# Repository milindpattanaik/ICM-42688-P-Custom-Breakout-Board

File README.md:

# ICM-42688-P Breakout Board

## Overview

### What is the ICM-42688-P?
The **ICM-42688-P** is a high-performance **6-axis Inertial Measurement Unit (IMU)** that integrates a **3-axis gyroscope** and a **3-axis accelerometer** in a compact package. It offers **low noise, high stability, and precision motion tracking**, making it ideal for applications like **drones, robotics, and industrial motion sensing**.  

The sensor supports both **I2C and SPI** communication, features **programmable digital filters, FIFO buffering, and low power consumption**, and includes **two interrupt pins** for efficient data handling. Its **temperature stability and low drift** make it well-suited for demanding applications requiring **accurate inertial measurements**.

### About This Project
This project is a **custom breakout board** for the ICM-42688-P, designed using **KiCad 8.0**. It includes:
- **Hardware**: A compact PCB with **I2C & SPI support**, onboard **3.3V LDO**, and **interrupt pins**.
- **Firmware**: Example code using **PlatformIO (Arduino framework)** for easy testing.
- **Testing Guide**: Steps to set up and read sensor data over I2C & SPI.

The driver used for interfacing with the **ICM-42688-P** is an open-source implementation developed by [Inhwan Wee ](https://github.com/finani) and is hosted on [https://github.com/finani/ICM42688](https://github.com/finani/ICM42688). This driver provides a well-structured and efficient way to communicate with the sensor over I2C or SPI, enabling seamless integration with Arduino and PlatformIO environments.

## Hardware Design
### Features:
- **Power Supply**: 3.3V LDO regulator onboard
- **Communication**: Supports both **I2C (SDA/SCL)** and **SPI (SCK, SDI, SDO, CS)**
- **Interrupts**: `INT1` and `INT2` available
- **Jumpers**: Select between I2C and SPI modes
- **Designed in**: KiCad 8.0
- **Tested on**: PlatformIO with Arduino framework

### Schematic

### PCB Layout

## Software

### Fixing `<cstdint>` Issues with AVR-GCC  

When compiling for AVR-based boards (e.g., **Arduino Uno, Mega, etc.**) using **AVR-GCC**, you may encounter the following error:  

```sh
fatal error: cstdint: No such file or directory
```

This happens because **AVR-GCC does not fully support C++ standard headers like `<cstdint>`**. This is a common defect in the arduino library.  

### Solution: Use `<stdint.h>` Instead  
The best solution is to replace `<cstdint>` with `<stdint.h>` in the `registers.h` file of the driver src code.  

❌ **Incorrect:**  
```cpp
#include <cstdint>  // This may cause issues with AVR-GCC
```
✅ **Correct:**  
```cpp
#ifdef AVR  // If compiling for AVR, define NO_CSTDINT to prevent including <cstdint>
# define NO_CSTDINT 1
#endif

// If NO_CSTDINT is NOT defined, include the standard C++ <cstdint>
#ifndef NO_CSTDINT
# include <cstdint>
#else
# include <stdint.h>

// If <cstdint> is unavailable, manually provide the needed types.
namespace std {
  using ::int8_t;           
  using ::uint8_t;         
                     
  using ::int16_t;         
  using ::uint16_t;       
                     
  using ::int32_t;         
  using ::uint32_t;       
}

#endif
```
✅ `<stdint.h>` is the **C version of `<cstdint>`** and is fully compatible with AVR-GCC.

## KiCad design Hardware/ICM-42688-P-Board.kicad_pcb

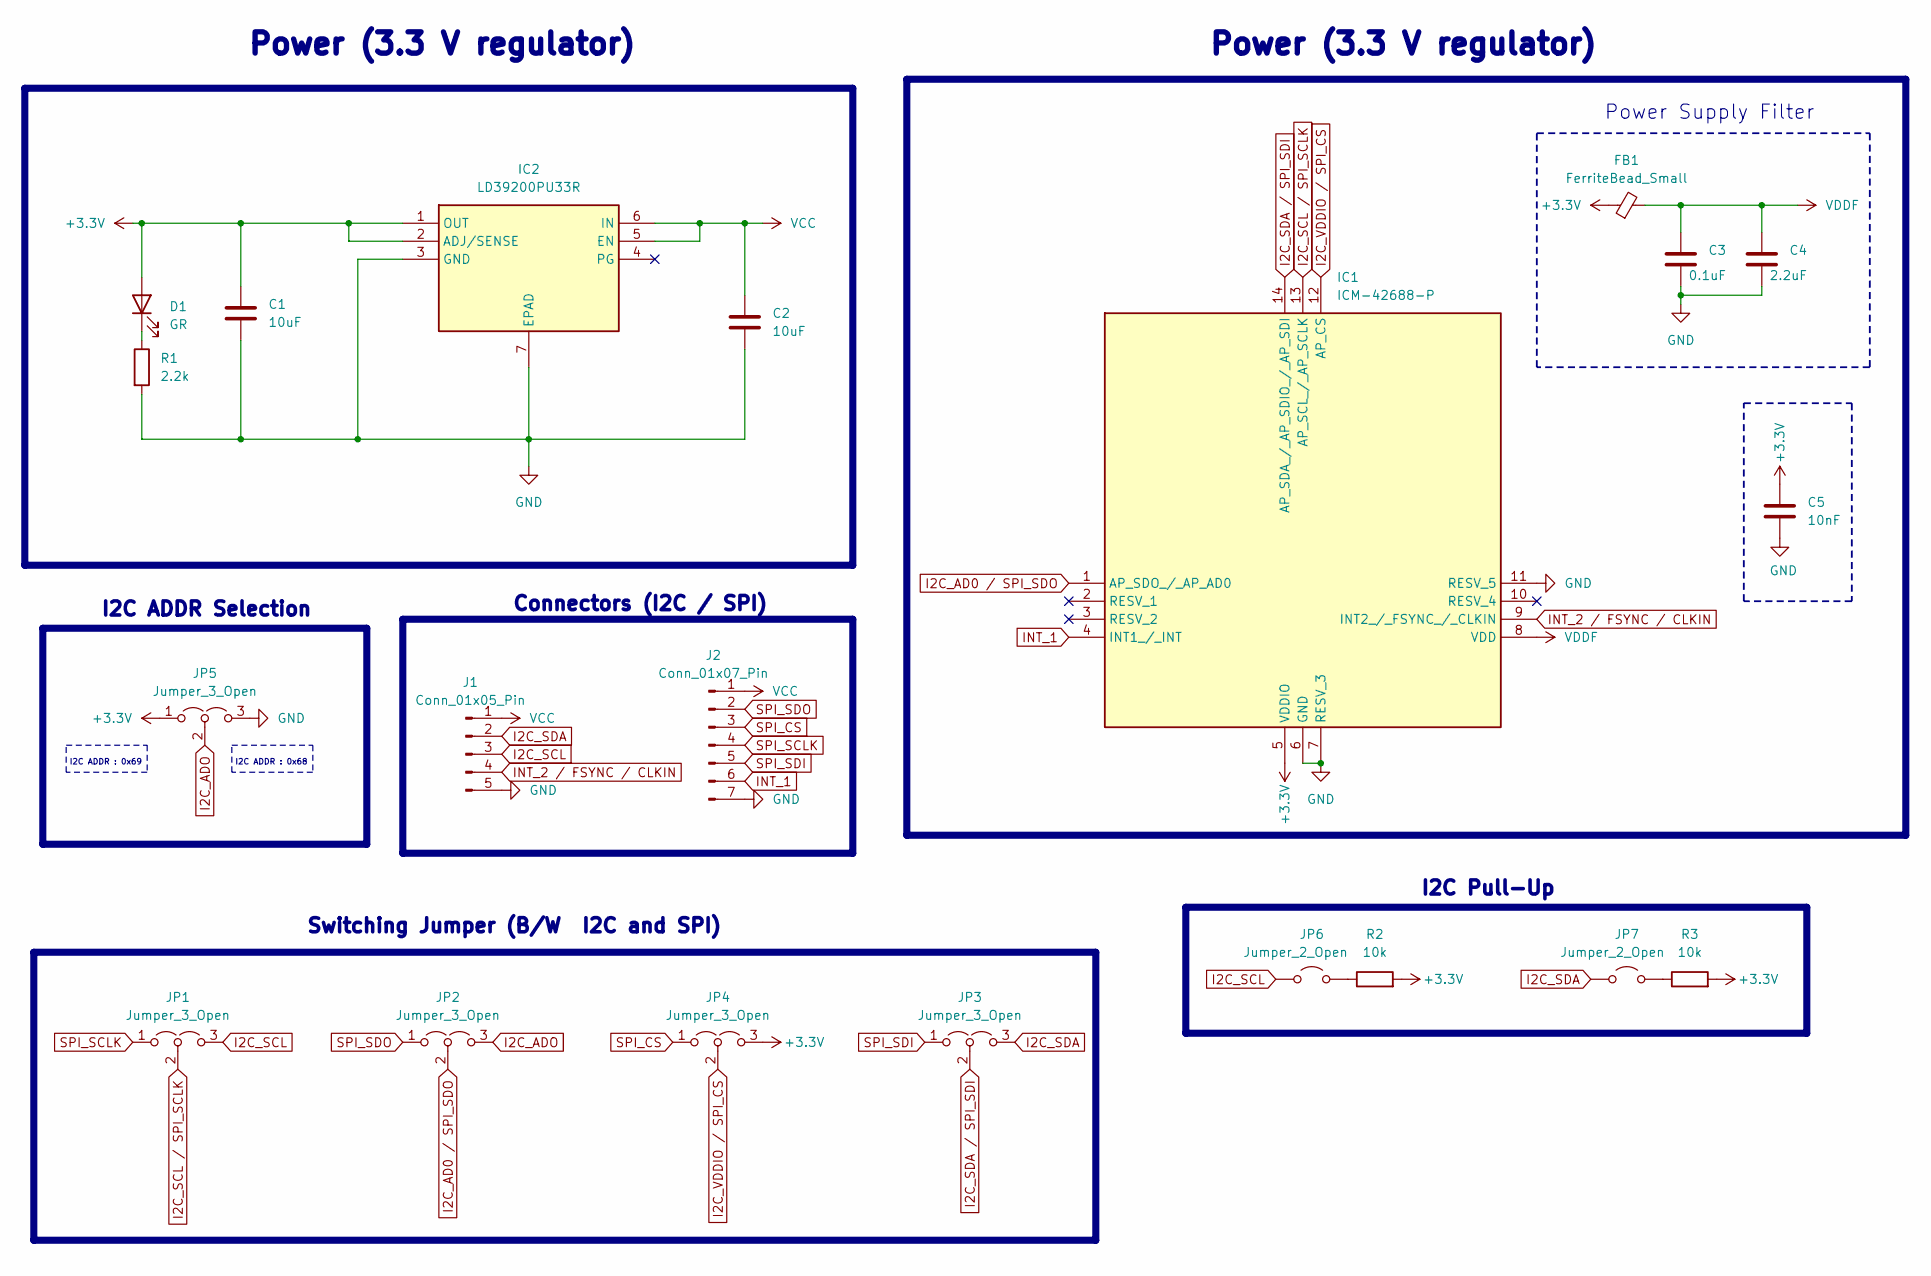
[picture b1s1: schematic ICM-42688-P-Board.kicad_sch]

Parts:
C1, C2: 10uF; C_0603_1608Metric
C3: 0.1uF; C_0402_1005Metric
C4: 2.2uF; C_0402_1005Metric
C5: 10nF; C_0402_1005Metric
D1: GR; LED_0603_1608Metric
FB1: FerriteBead_Small; L_0603_1608Metric
IC1: ICM-42688-P; IIM42352; Mouser Part Number 410-ICM-42688-P
IC2: LD39200PU33R; SON95P300X300X100-7N-D; Mouser Part Number 511-LD39200PU33R
J1: Conn_01x05_Pin; PinHeader_1x05_P2.54mm_Vertical
J2: Conn_01x07_Pin; PinHeader_1x07_P2.54mm_Vertical
JP1, JP2, JP3, JP4, JP5: Jumper_3_Open; PinHeader_1x03_P2.54mm_Vertical
JP6, JP7: Jumper_2_Open; PinHeader_1x02_P2.54mm_Vertical
R1: 2.2k; R_0402_1005Metric
R2, R3: 10k; R_0603_1608Metric

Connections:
+3.3V: C1.1, C5.1, D1.2 (A), FB1.1, IC1.5 (VDDIO), IC2.1 (OUT), IC2.2 (ADJ/SENSE), JP4.3 (B), JP5.1 (A), R2.2, R3.2
GND: C1.2, C2.2, C3.2, C4.2, C5.2, IC1.6 (GND), IC1.7 (RESV_3), IC1.11 (RESV_5), IC2.3 (GND), IC2.7 (EPAD), J1.5, J2.7, JP5.3 (B), R1.2; also elsewhere on the board
I2C_AD0 / SPI_SDO: IC1.1 (AP_SDO_/_AP_AD0), JP2.2 (C)
I2C_ADO: JP2.3 (B), JP5.2 (C)
I2C_SCL: J1.3, JP1.3 (B), JP6.1 (A)
I2C_SCL / SPI_SCLK: IC1.13 (AP_SCL_/_AP_SCLK), JP1.2 (C)
I2C_SDA: J1.2, JP3.3 (B), JP7.1 (A)
I2C_SDA / SPI_SDI: IC1.14 (AP_SDA_/_AP_SDIO_/_AP_SDI), JP3.2 (C)
I2C_VDDIO / SPI_CS: IC1.12 (AP_CS), JP4.2 (C)
INT_1: IC1.4 (INT1_/_INT), J2.6
INT_2 / FSYNC / CLKIN: IC1.9 (INT2_/_FSYNC_/_CLKIN), J1.4
unnamed: D1.1 (K), R1.1
unnamed: JP6.2 (B), R2.1
unnamed: JP7.2 (B), R3.1
SPI_CS: J2.3, JP4.1 (A)
SPI_SCLK: J2.4, JP1.1 (A)
SPI_SDI: J2.5, JP3.1 (A)
SPI_SDO: J2.2, JP2.1 (A)
VCC: C2.1, IC2.5 (EN), IC2.6 (IN), J1.1, J2.1
VDDF: C3.1, C4.1, FB1.2, IC1.8 (VDD)

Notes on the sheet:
Power Supply Filter
I2C ADDR : 0x69
I2C Pull-Up
I2C ADDR Selection
Power (3.3 V regulator)
Connectors (I2C / SPI)
I2C ADDR : 0x68
Switching Jumper (B/W I2C and SPI)

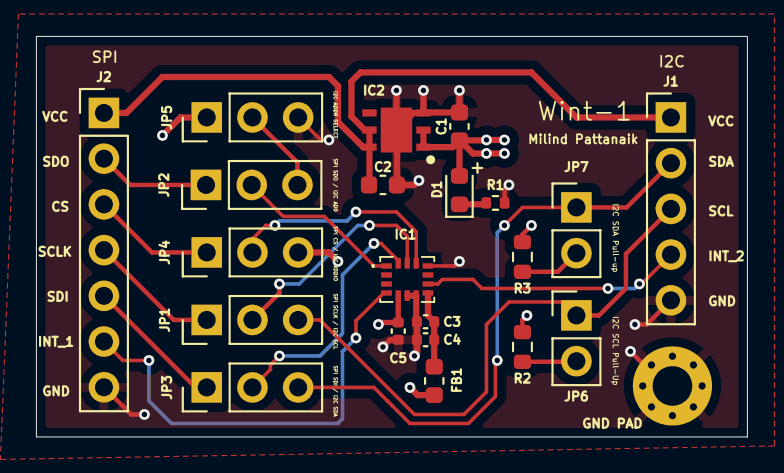
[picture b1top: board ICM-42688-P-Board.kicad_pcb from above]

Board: 4 copper layers, 39.5 x 22.2 mm, 22 parts (0 on the bottom side), 20 nets.

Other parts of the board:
GND PAD: MountingHole_2.2mm_M2_Pad_Via

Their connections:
GND: GND PAD.1; also elsewhere on the board

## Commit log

2025-02-26 feat: add ICM-42688-P-Custom-Breakout-Board project
    add the ICM-42688-P-Custom-Breakout-Board Project which includes the hardware and arduino software to test
2025-02-26 docs: update readme
    update readme
2025-02-26 feat: add SPI code
    add SPI code for ICM-42688-P
2025-02-26 docs: update readme
    updated readme on the software section
2025-02-26 docs: update readme
    misc update readme
2025-02-26 Create LICENSE
